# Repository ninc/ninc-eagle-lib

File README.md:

# ninc-eagle-lib
My collection of Eagle libraries
## Supported libraries (soldering untested)
* Sensirion SHTC1 (http://www.sensirion.com/en/products/humidity-temperature/download-center/)
* 
## Currently working on:
*

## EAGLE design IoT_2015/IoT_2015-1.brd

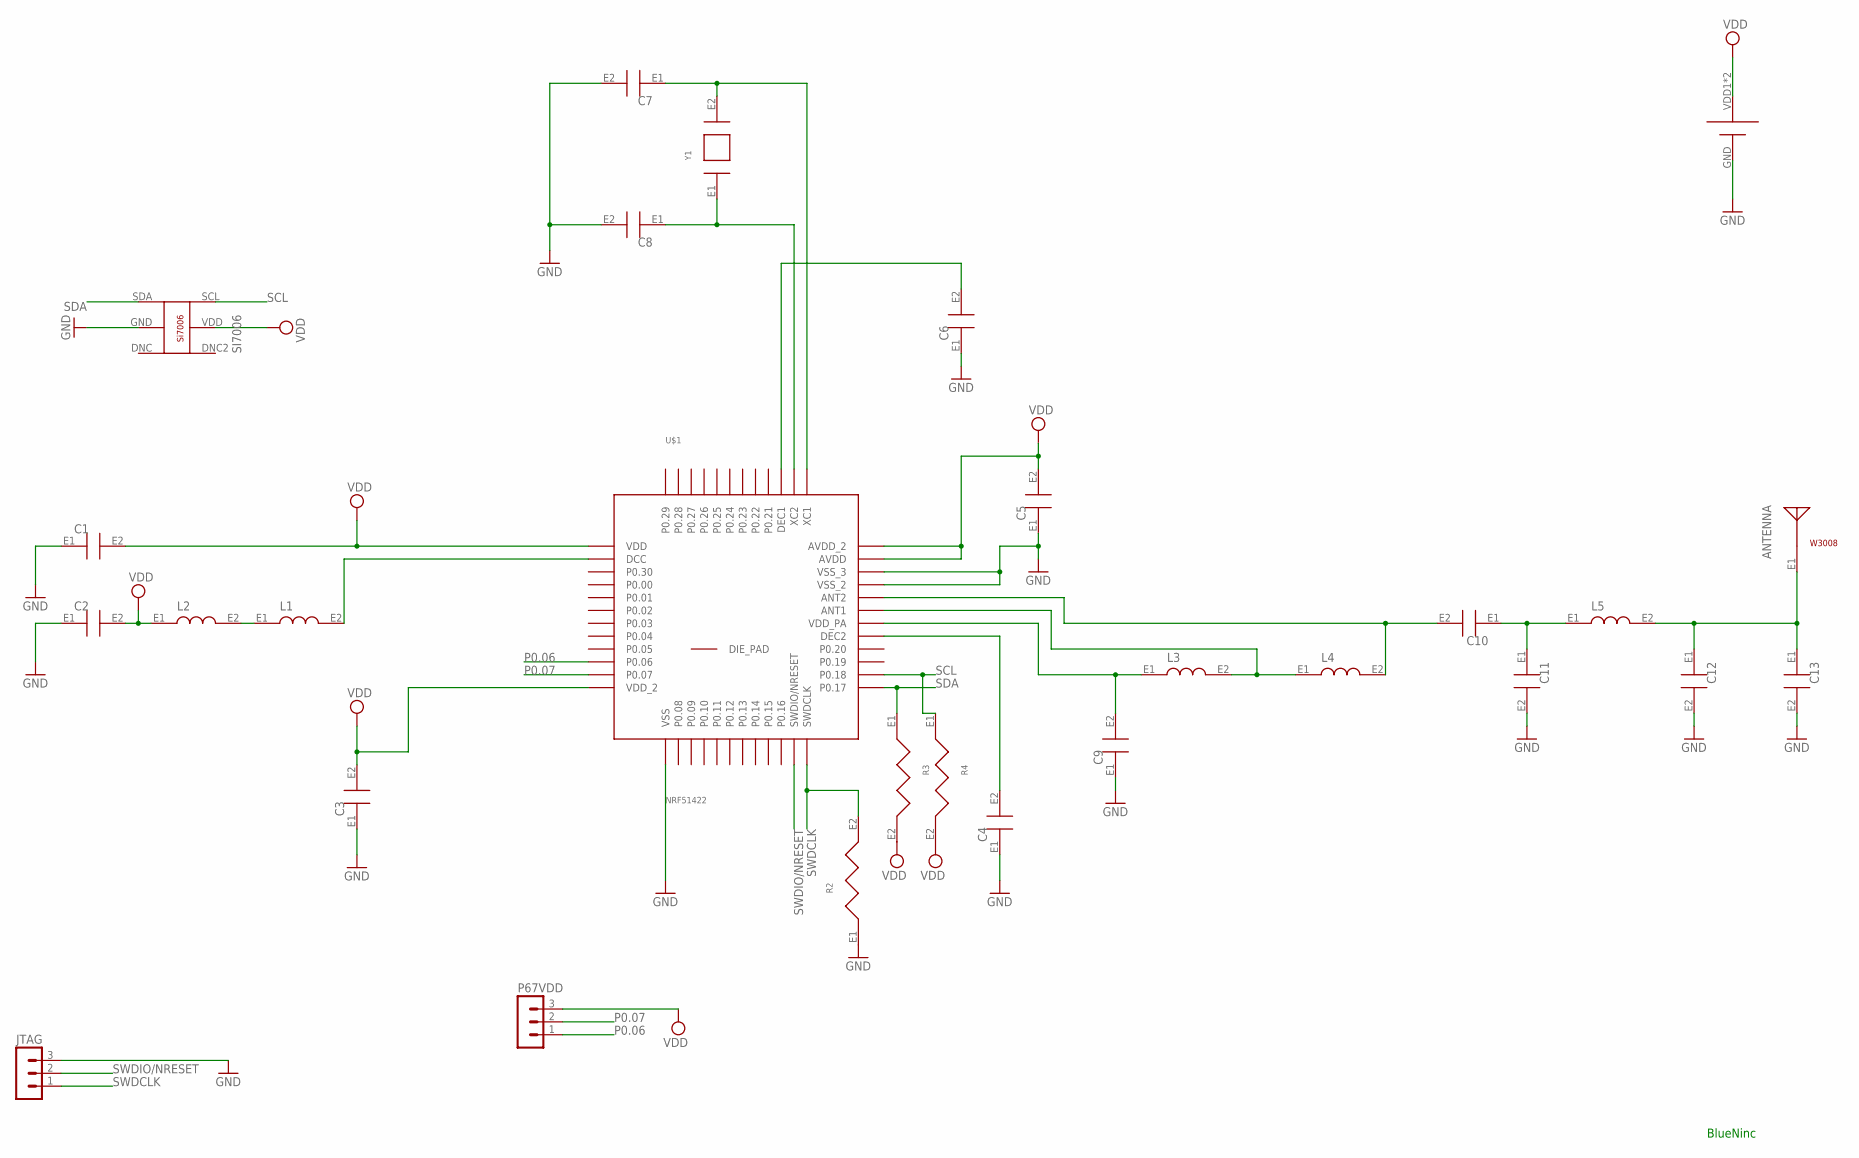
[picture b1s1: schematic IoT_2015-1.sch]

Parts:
ANTENNA: W3008
BATTERY: BAT-HLD-001
C1, C2, C3, C4, C5, C6, C7, C8, C9, C10, C11, C12, C13: VJ1603_W1BC
JTAG: MA03-1
L1, L2, L3, L4, L5: JTI_CAT_2012_INDUCTORS_CHIP-242427
P67VDD: MA03-1
R2, R3, R4: ERJ-3GEYJ103V
SI7006: SI7006-A20-IM
U$1: NRF51422; QFN48
Y1: ABLS-16.000MHZ-B4-T

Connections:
GND: BATTERY.GND, C1.E1, C2.E1, C3.E1, C4.E1, C5.E1, C6.E1, C7.E2, C8.E2, C9.E1, C11.E2, C12.E2, C13.E2, JTAG.3, R2.E1, SI7006.GND, U$1.13 (VSS), U$1.33 (VSS_2), U$1.34 (VSS_3)
unnamed: L1.E1, L2.E2
unnamed: L1.E2, U$1.2 (DCC)
unnamed: C4.E2, U$1.29 (DEC2)
unnamed: ANTENNA.E1, C12.E1, C13.E1, L5.E2
unnamed: C9.E2, L3.E1, U$1.30 (VDD_PA)
unnamed: L3.E2, L4.E1, U$1.31 (ANT1)
unnamed: C10.E2, L4.E2, U$1.32 (ANT2)
unnamed: C6.E2, U$1.39 (DEC1)
unnamed: C8.E1, U$1.38 (XC2), Y1.E1
unnamed: C7.E1, U$1.37 (XC1), Y1.E2
unnamed: C10.E1, C11.E1, L5.E1
P0.06: P67VDD.1, U$1.10 (P0.06)
P0.07: P67VDD.2, U$1.11 (P0.07)
SCL: R4.E1, SI7006.SCL, U$1.26 (P0.18)
SDA: R3.E1, SI7006.SDA, U$1.25 (P0.17)
SWDCLK: JTAG.1, R2.E2, U$1.24 (SWDCLK)
SWDIO/NRESET: JTAG.2, U$1.23 (SWDIO/NRESET)
VDD: BATTERY.VDD1 (VDD), BATTERY.VDD2 (VDD), C1.E2, C2.E2, C3.E2, C5.E2, L2.E1, P67VDD.3, R3.E2, R4.E2, SI7006.VDD, U$1.1 (VDD), U$1.12 (VDD_2), U$1.35 (AVDD), U$1.36 (AVDD_2)

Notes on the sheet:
BlueNinc

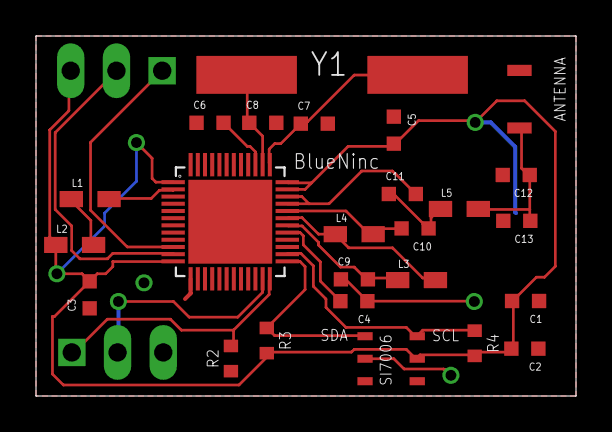
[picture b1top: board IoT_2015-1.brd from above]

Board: 2 copper layers, 30.0 x 20.0 mm, 28 parts (1 on the bottom side), 19 nets.

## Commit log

2015-07-27 Added Sensirion SHTC1
2015-08-22 test
    la till txtfil testar
2015-08-22 Adding footprints
    Added SMD footprints for capacitors with the standard VJ1603_W1BC from
    manufacturer Vishay
2015-08-24 ERJ-3GEYJ103V
    Adding a footprint for SMD resistors with 1603 shape
2015-08-25 Added footprint for oscillator 32KHz
2015-08-26 Added Si7006 sensor
2015-08-26 Added Pulse antenna W3008
2015-08-29 Added Renate battery holder
2015-08-29 Added more components
    Components
2015-08-30 evaluation kit nrf51822
    added library for evaluation kit nrf51822
2015-08-30 Refining
    Refined the libraries with prefix, centering of position and correct
    name stamp
2015-08-30 Refining
    Refined the library path for all components, added the names correctly
    to connect properly with the given prefix in device package
2015-08-30 The schematic
    Added the beginning of the schematic, however- a crystal needs to be
    changed from 15Mhz to 16Mhz-
2015-08-30 Refining
    The 15Mhz crystal is replaced with footprint for 16Mhz crystal.
2015-09-01 Added sensor, battery and antenna to schematic
2015-09-01 Finished the schematic
    Refined the shematic with I2C-resistors for SDA and SCL, additional pins
    for unused I/O:s.
2015-09-01 Correction with ERC
    Correction carried out with ERC
2015-09-01 BoardLayout
    Fixed the layer-property of battery and started the board-layout.
2015-09-01 First board design finished
2015-09-03 Refining
    Changed the battery holder, deleted some pinheaders
2015-09-03 Finished design
2015-09-13 Routed by hand
2015-09-13 Layout
    Boardlayout is finished, the Gerberfile needs to be created.
2015-09-13 Gerberfiles
    Generated gerber files with OSHPark-2layer-Eagle7.2.cam file from OSH
    Park. Following guide for this:
    http://support.oshpark.com/support/articles/134816-generating-custom-gerbers-from
    A zip file is now available, "GerberFiles.zip" in root dir. Send it to
    OSH Park for PCB manufacturing...
2015-09-13 Generated new gerber files
2015-09-13 Added gerber.rar
2015-09-13 Added gerber in zip format also
2015-09-13 Removed old gerber files
2015-09-21 FITT EAGLE
2015-09-21 Test av jordlager
    titta på dennna?
2015-09-21 groundplane
    groundplane for top and bottom layer are done. To adjust the width of
    the copper pour: Set the width of the polygon to draw around the design.
2015-09-22 Uploaded gerber files
2015-09-28 Generated gerberfile
    Autoroute and generate ground pour layer were carried out. Check the
    gerberfile.
2015-09-29 Updated design with GND bottom layer
2015-10-03 Stop masks are corrected
    All DRC errors are corrected. Specially the stop masks have been
    corrected in the footprints of interest.
